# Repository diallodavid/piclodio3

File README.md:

# Hardware version of Piclodio3

This version of [Piclodio3](https://github.com/Sispheor/piclodio3) is hardware version of the alarm clock with a web radio player.
It should be installed on Raspberry Pi with:
- [ReSpeaker 2-Mics Pi HAT](https://wiki.seeedstudio.com/ReSpeaker_2_Mics_Pi_HAT)
- MAX7219 8x32 4 in 1 Dot Matrix LED Display Module
- PCF8591 ADC+DAC combo

As in the Piclodio3 project, you can add url stream to complete the collection. Scheduling alarm clock is easy and can be periodic.
A local backup MP3 file is used in case of losing internet connection or if the web radio is not anymore available to be sure you'll be awaken.

## Installation

### Install seeed-voicecard (ReSpeaker 2-Mics Pi HAT)

Check [this doc](doc/install_seeed-voicecard_rpi.md) to install ReSpeaker 2-Mics Pi HAT on your RPI.

### Via Docker

The project can be deployed via the provided docker compose file. Check [this doc](doc/install_docker_rpi.md) to install Docker and docker-compose on your RPI.
```
git clone https://github.com/diallodavid/piclodio3.git
cd piclodio3
docker-compose up -d
```

Then access the UI via your web browser with the IP of your host (type `ip a` to get it). E.g: "http://192.168.0.22/"

### Development env

The project is split in tihree parts:
- [Backend based on Django Rest Framework](back/README.md)
- [Frontend based on Angular 11.1.1](front/README.md)
- [Device](device/README.md)

Installation procedures have been tested on a Raspberry Pi and on Debian GNU/Linux 10 (buster) but the project should works on any Linux system that can handle Django and Angular.

## Web Radio URLs

There is a lot of web radio online. In most of case, websites provide a `pls` or `m3u` file that contain the URL you need to give to Piclodio.
You can also get the URL from the console of your web browser. Look for the URL that consume the most brandwith in the network console.

Take a look to [internet-radio.com](https://www.internet-radio.com/) for a large selection of web radio sorted by genre.
Or [fluxradios](http://fluxradios.blogspot.com/).

## API doc

You can accees to API doc on the "/redoc" URL.

## Timezone

By default the time is showed in UTC. If you want to change the timezone, update the file `piclodio3/back/piclodio3/settings.py`
E.g:
```
TIME_ZONE = 'Europe/Paris'
```

## Contribute

Fell free to open an issue to ask a new feature or raise a bug.

## License

Copyright (c) 2021. All rights reserved.

Piclodio is covered by the MIT license, a permissive free software license that lets you do anything you want with the source code, as long as you provide back attribution and "don't hold you liable". For the full license text see the [LICENSE.md](LICENSE.md) file.

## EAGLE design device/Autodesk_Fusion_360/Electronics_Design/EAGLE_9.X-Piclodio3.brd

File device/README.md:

# Piclodio 3 device

## Development installation

Create a dedicated python env
```
cd device
virtualenv venv -p python3.7
source venv/bin/activate
```

Install python packages
```
pip3 install -r requirements.txt
pip3 install luma.emulator==1.4.0
pip3 install pynput==1.7.2
```

## Run dev server

# Run tests

## Production server

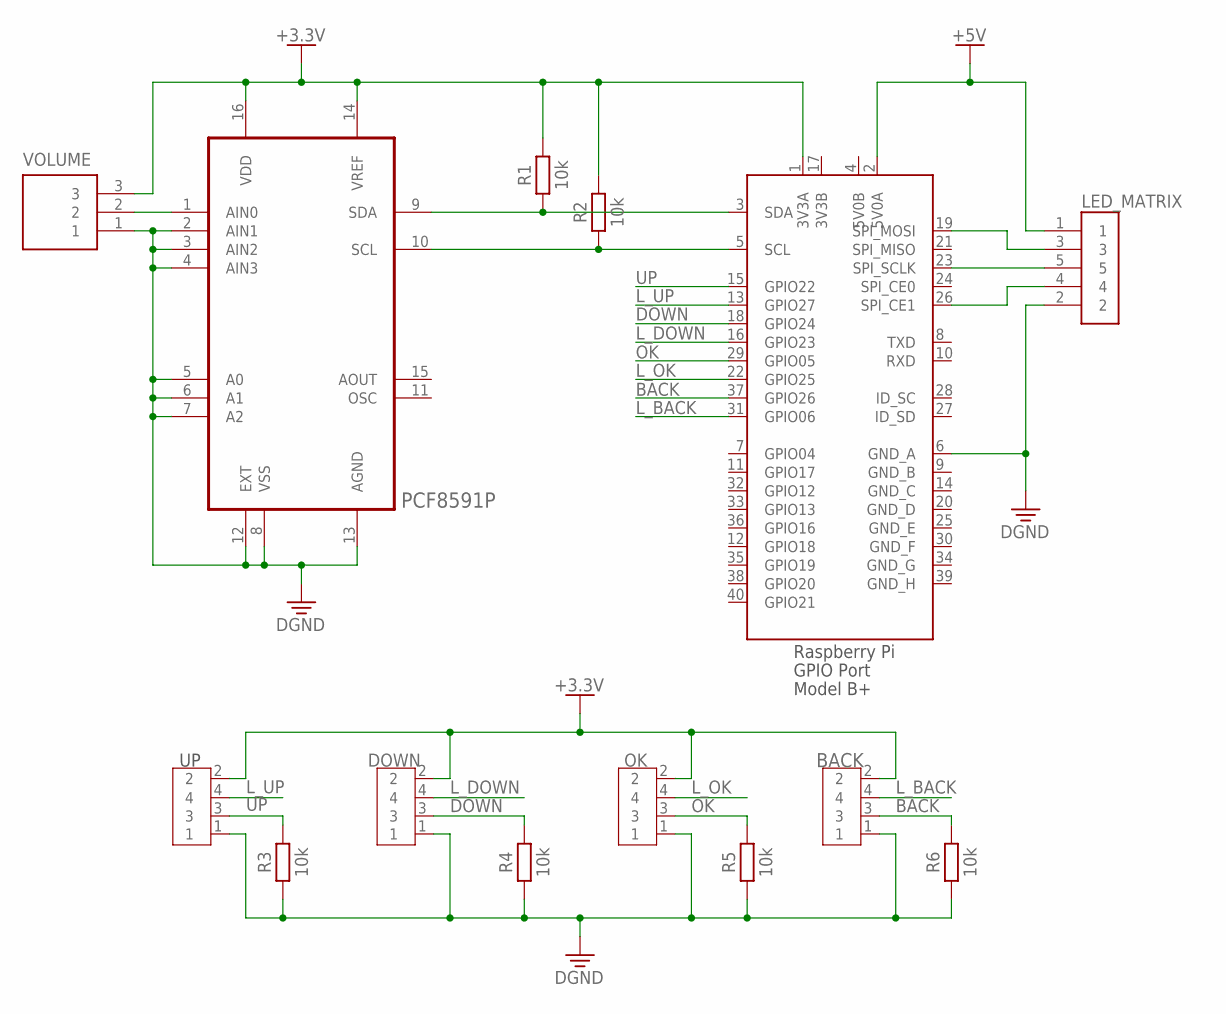
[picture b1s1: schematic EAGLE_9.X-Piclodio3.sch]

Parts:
BACK: 3A/250V; B4B-XH-A
DOWN: 3A/250V; B4B-XH-A
LED_MATRIX: S5B-XH-A(LF)(SN); JST_S5B-XH-A(LF)(SN)
OK: 3A/250V; B4B-XH-A
R1, R2, R3, R4, R5, R6: 10k; RESAD1176W63L850D250B
U2: PCF8591P; DIP254P762X420-16
UP: 3A/250V; B4B-XH-A
VOLUME: S3B-XH-A(LF)(SN); JST_S3B-XH-A(LF)(SN)
X1: RASPI_BOARD_B+#_H; RASPI_BOARD_B+HAT

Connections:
+3.3V: BACK.2, DOWN.2, OK.2, R1.2, R2.1, U2.14 (VREF), U2.16 (VDD), UP.2, VOLUME.3, X1.1 (3V3A)
+5V: LED_MATRIX.1, X1.2 (5V0A)
BACK: BACK.3, R6.2, X1.37 (GPIO26)
DGND: BACK.1, DOWN.1, LED_MATRIX.2, OK.1, R3.1, R4.1, R5.1, R6.1, U2.2 (AIN1), U2.3 (AIN2), U2.4 (AIN3), U2.5 (A0), U2.6 (A1), U2.7 (A2), U2.8 (VSS), U2.12 (EXT), U2.13 (AGND), UP.1, VOLUME.1, X1.6 (GND_A)
DOWN: DOWN.3, R4.2, X1.18 (GPIO24)
L_BACK: BACK.4, X1.31 (GPIO06)
L_DOWN: DOWN.4, X1.16 (GPIO23)
L_OK: OK.4, X1.22 (GPIO25)
L_UP: UP.4, X1.13 (GPIO27)
unnamed: U2.1 (AIN0), VOLUME.2
unnamed: R2.2, U2.10 (SCL), X1.5 (SCL)
unnamed: R1.1, U2.9 (SDA), X1.3 (SDA)
unnamed: LED_MATRIX.5, X1.23 (SPI_SCLK)
unnamed: LED_MATRIX.3, X1.19 (SPI_MOSI)
unnamed: LED_MATRIX.4, X1.26 (SPI_CE1)
OK: OK.3, R5.2, X1.29 (GPIO05)
UP: R3.2, UP.3, X1.15 (GPIO22)

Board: 2 copper layers, 14 parts (0 on the bottom side), 17 nets, no tracks yet.

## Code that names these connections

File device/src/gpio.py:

import logging
import RPi.GPIO as GPIO

logger = logging.getLogger(__name__)

class Gpio:
  UP     = 22 # Up
  L_UP   = 27 # Light up
  DOWN   = 24 # Down
  L_DOWN = 23 # Light down
  OK     = 5  # Ok
  L_OK   = 25 # Light ok
  BACK   = 26 # Back
  L_BACK = 6  # Light back

  def __init__(self, down=None, up=None, ok=None, back=None):
    GPIO.setmode(GPIO.BCM)
    
    GPIO.setup(self.L_UP,   GPIO.OUT)
    GPIO.setup(self.L_DOWN, GPIO.OUT)
    GPIO.setup(self.L_OK,   GPIO.OUT)
    GPIO.setup(self.L_BACK, GPIO.OUT)

    GPIO.setup(self.UP,   GPIO.IN, pull_up_down=GPIO.PUD_DOWN)
    GPIO.setup(self.DOWN, GPIO.IN, pull_up_down=GPIO.PUD_DOWN)
    GPIO.setup(self.OK,   GPIO.IN, pull_up_down=GPIO.PUD_DOWN)
    GPIO.setup(self.BACK, GPIO.IN, pull_up_down=GPIO.PUD_DOWN)

    if down: 
      self.down = down
      GPIO.output(self.L_DOWN, GPIO.HIGH) 
      GPIO.add_event_detect(self.DOWN, GPIO.RISING, callback=self.__down, bouncetime=200)

    if up: 
      self.up = up
      GPIO.output(self.L_UP, GPIO.HIGH) 
      GPIO.add_event_detect(self.UP, GPIO.RISING, callback=self.__up, bouncetime=200)

    if ok: 
      self.ok = ok
      GPIO.output(self.L_OK, GPIO.HIGH) 
      GPIO.add_event_detect(self.OK, GPIO.RISING, callback=self.__ok, bouncetime=200)

    if back: 
      self.back = back
      GPIO.output(self.L_BACK, GPIO.HIGH) 
      GPIO.add_event_detect(self.BACK, GPIO.RISING, callback=self.__back, bouncetime=200)
    logger.debug('GPIO created')

  def stop(self):
    # Destructor does not work with GPIO.setup
    GPIO.remove_event_detect(self.DOWN)
    GPIO.remove_event_detect(self.UP)
    GPIO.remove_event_detect(self.OK)
    GPIO.remove_event_detect(self.BACK)

    GPIO.output(self.L_DOWN, GPIO.LOW) 
    GPIO.output(self.L_UP,   GPIO.LOW) 
    GPIO.output(self.L_OK,   GPIO.LOW) 
    GPIO.output(self.L_BACK, GPIO.LOW) 
    logger.debug('GPIO all events removed')

  def __down(self, channel):
    logger.debug('GPIO down <%d>',channel)
    self.down()
  
  def __up(self, channel):
    logger.debug('GPIO up <%d>',channel)
    self.up()
  
  def __ok(self, channel):
    logger.debug('GPIO ok <%d>',channel)
    self.ok()
  
  def __back(self, channel):
    logger.debug('GPIO back <%d>',channel)
    self.back()

if __name__ == "__main__":
  logging.basicConfig(level=logging.DEBUG)

  def cbk():
    pass

  gpio = Gpio(ok=cbk,back=cbk,up=cbk,down=cbk)

  while 1:
    pass

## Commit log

2021-01-12 Initial device commit
2021-01-18 Add device container in docker-compose.yml
2021-01-18 Fix issue backend API on the port 8000
2021-01-18 Use Docker Hub image instead of local image
2021-01-18 Update backend image and use diallodavid Docker Hub repository
2021-02-02 upgrade to Angular 10.2.1
2021-02-02 upgrade to Angular 11.1.1
2021-02-07 use hostname to get back the appropriate container’s IP address
2021-02-10 correct hostname
2021-02-14 use local clock instead of backend one
2021-02-15 Update frontend image and use diallodavid Docker Hub repository
2021-02-26 Integrate ReSpeaker 2-Mics Pi HAT as Speaker
2021-02-26 Prepare amd64 version of device
2021-02-27 Customize Radio list and asoundrc file
2021-03-04 Update device image and use diallodavid Docker Hub repository
2021-03-04 Fix issue in radio list and set DEBUG in Piclodio 3 backend to False
2021-03-06 Update documentation
2021-03-06 Replace asoundrc by the output of alsactl
2021-03-06 Correct path error
2021-03-07 Remove update and upgrade of the system
2021-03-07 Fix Rust issue in docker-compose installation
2021-03-07 Specify sound card for Mplayer
2021-03-07 Fix issues in device
2021-03-07 Remove useless upgrade system
2021-03-27 Change output GPIO into pull down
2021-03-29 Fix debug block
2021-04-08 Add light buttons and change GPIO pinout of buttons
2021-04-09 Manage light buttons
2021-04-09 Change GPIO pinout of buttons
2021-05-02 Add electronics design of Piclodio3 device
2021-06-20 Add electronics design in KiCad of Piclodio3 device
2021-06-20 Remove useless components
